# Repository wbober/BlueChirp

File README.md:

BlueChirp!
==========

A soil moisture sensor based on nRF52. Uses capacitive sensing for measurements
and Bluetooth Low Energy to send the readings.

The is work in progess. PCB is done and ordered, firmware yet to come.

Based on Chirp! designed by Albertas Mickėnas. Find out more here:
https://github.com/Miceuz/PlantWateringAlarm
https://wemakethings.net/chirp/

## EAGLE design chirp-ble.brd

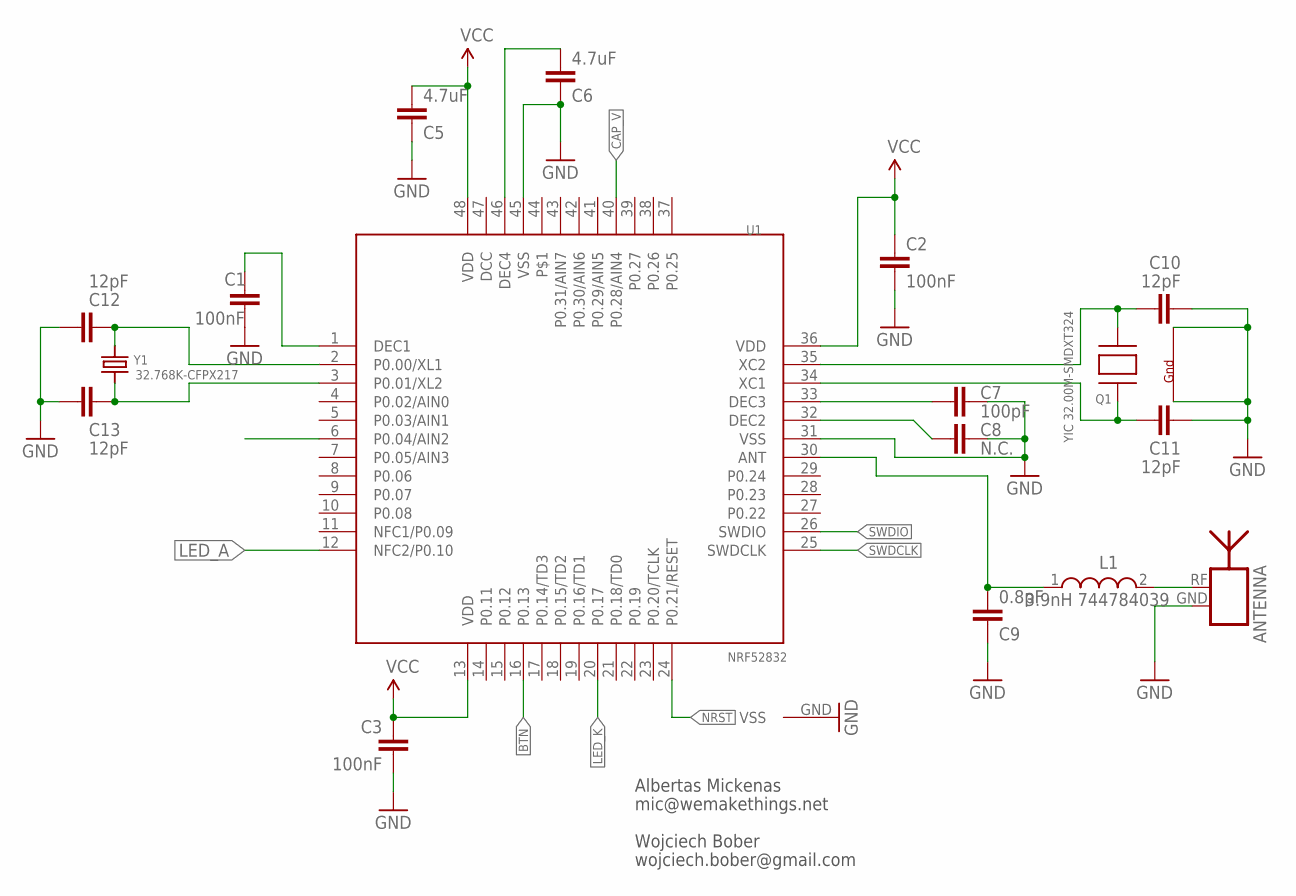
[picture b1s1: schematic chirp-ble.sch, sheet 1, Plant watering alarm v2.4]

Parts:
ANTENNA: ANTENNA_1RIGHT; SWRA117D_RIGHT
C1, C2, C3: 100nF; C0402
C5, C6: 4.7uF; C0402
C7: 100pF; C0402
C8: N.C.; C0402
C9: 0.8pF; C0402
C10, C11, C12, C13: 12pF; C0402
L1: 3.9nH 744784039; WE-MK_0402
Q1: YIC 32.00M-SMDXT324; NX3225
U1: NRF52832; QFN48
Y1: 32.768K-CFPX217; ABS07

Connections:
ANT: C9.2, L1.1, U1.30 (ANT)
BTN: U1.16 (P0.13); also elsewhere on the board
CAP_V: U1.40 (P0.28/AIN4); also elsewhere on the board
CLK_OUT: U1.6 (P0.04/AIN2); also elsewhere on the board
DCC: U1.47 (DCC)
GND: ANTENNA.GND, C1.2, C2.2, C3.2, C5.1, C6.1, C7.2, C8.2, C9.1, C10.2, C11.2, C12.2, C13.1, Q1.2 (G2), Q1.4 (G1), U1.31 (VSS), U1.45 (VSS), U1.GND (VSS); also elsewhere on the board
LED_A: U1.12 (NFC2/P0.10); also elsewhere on the board
LED_K: U1.20 (P0.17); also elsewhere on the board
unnamed: C8.1, U1.32 (DEC2)
unnamed: C10.1, Q1.3 (X2), U1.35 (XC2)
unnamed: ANTENNA.RF, L1.2
unnamed: C11.1, Q1.1 (X1), U1.34 (XC1)
unnamed: C1.1, U1.1 (DEC1)
unnamed: C6.2, U1.46 (DEC4)
unnamed: C7.1, U1.33 (DEC3)
NRST: U1.24 (P0.21/RESET); also elsewhere on the board
P$1: U1.44
SWDCLK: U1.25 (SWDCLK); also elsewhere on the board
SWDIO: U1.26 (SWDIO); also elsewhere on the board
VCC: C2.1, C3.1, C5.2, U1.13 (VDD), U1.36 (VDD), U1.48 (VDD); also elsewhere on the board
Y1_M: C13.2, U1.3 (P0.01/XL2), Y1.1
Y1_P: C12.1, U1.2 (P0.00/XL1), Y1.2

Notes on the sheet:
Albertas Mickenas
mic@wemakethings.net
Wojciech Bober
wojciech.bober@gmail.com

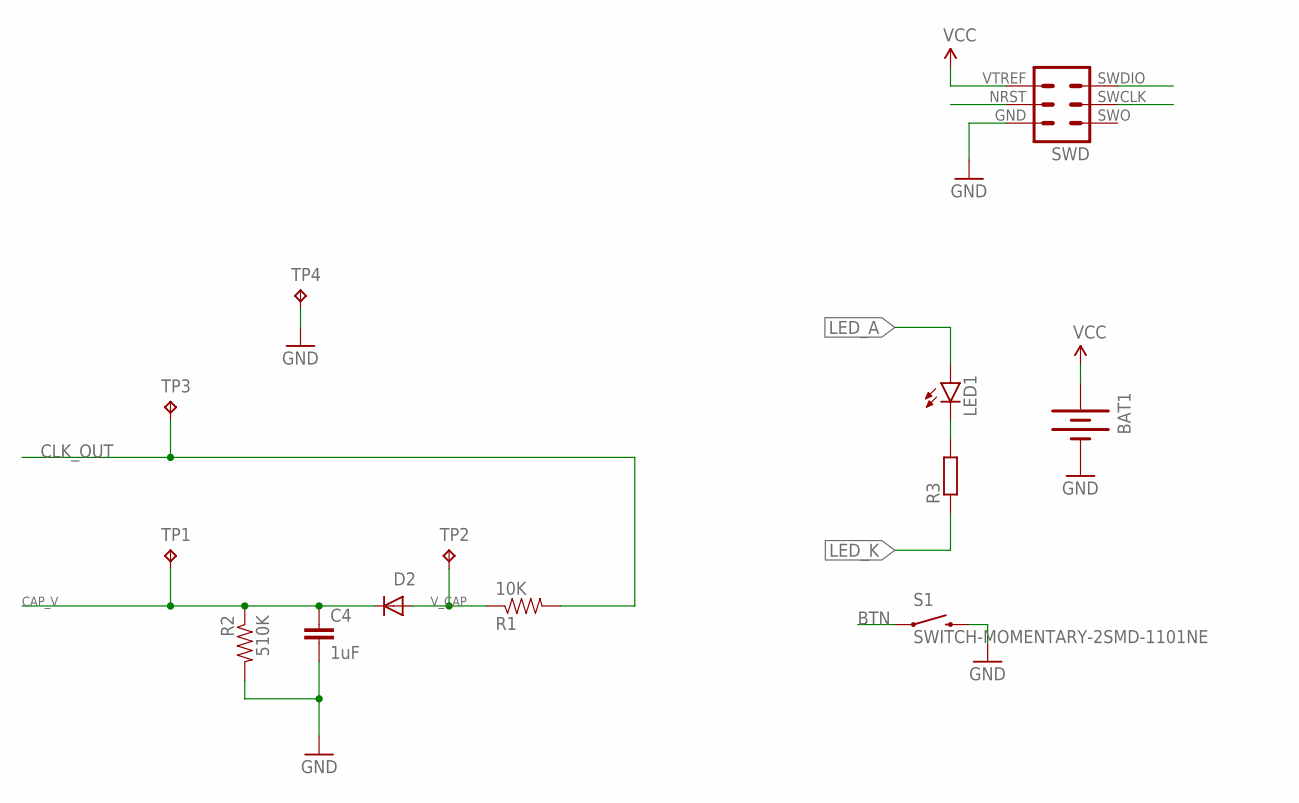
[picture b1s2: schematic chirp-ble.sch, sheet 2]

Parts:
BAT1: BATTERY12MM; BATTCON_12MM
C4: 1uF; 0603-CAP
D2: DIODE-SCHOTTKY_; SOD-523
LED1: LED0603; LED-0603
R1: 10K; 0603-RES
R2: 510K; 0603-RES
R3: R-EU_R0402; R0402
S1: SWITCH-MOMENTARY-2SMD-1101NE; TACTILE-SWITCH-1101NE
SWD: SWD; MA03-2
TP1, TP2, TP3, TP4: TPB1,27; B1,27

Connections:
BTN: S1.1; also elsewhere on the board
CAP_V: C4.1, D2.K (C), R2.1, TP1.TP; also elsewhere on the board
CLK_OUT: R1.2, TP3.TP; also elsewhere on the board
GND: BAT1.GND (-), C4.2, R2.2, S1.2, SWD.GND, TP4.TP; also elsewhere on the board
LED_A: LED1.A; also elsewhere on the board
LED_K: R3.1; also elsewhere on the board
unnamed: LED1.C, R3.2
NRST: SWD.NRST (NRESET); also elsewhere on the board
SWDCLK: SWD.SWCLK; also elsewhere on the board
SWDIO: SWD.SWDIO; also elsewhere on the board
VCC: BAT1.PWR@1 (+), BAT1.PWR@2 (+), SWD.VTREF; also elsewhere on the board
V_CAP: D2.A, R1.1, TP2.TP

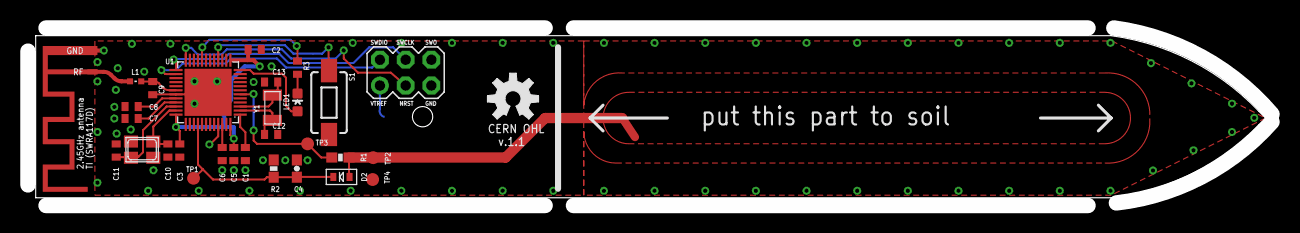
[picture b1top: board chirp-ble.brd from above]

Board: 2 copper layers, 122.8 x 17.5 mm, 30 parts (1 on the bottom side), 22 nets.

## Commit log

2015-11-09 Fully routed
2015-11-09 DRC and ERC
2015-11-09 Added panel
2015-11-11 Spike
2016-10-24 Changed min drill size to 0.4mm
2016-10-24 Added fabrication data

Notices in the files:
chirp-ble.brd:
CERN OHL
parts and their libraries:
SignalCommunications: Copyright: Würth Elektronik
SparkFun-LED: Licensing: Creative Commons ShareAlike 4.0 International - https://creativecommons.org/licenses/by-sa/4.0
